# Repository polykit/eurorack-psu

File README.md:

# Eurorack Power Supply

This repository contains KiCad schematics and PCB layout for an Eurorack power supply. It delivers +12V, -12V and +5V. A 12V AC/AC 1A to 2A wall wart power supply is needed. Gerber files can be found [here](plots/)

## BOM

|Reference               |Quantity|Value                                             |
|------------------------|--------|--------------------------------------------------|
|C1 C2 C3 C4 C5 C6       |6       |3300uF                                            |
|C9 C10 C12              |3       |100uF                                             |
|C7 C8 C11               |3       |1uF                                               |
|D1 D2 D3 D4 D5 D6 D7 D8 |8       |1N4004                                            |
|D9                      |1       |LED 5mm                                           |
|J1                      |1       |Barrel Jack Socket 5.5mm/2.1mm                    |
|J2                      |1       |IDC 16-pin                                        |
|J3                      |1       |2-pin 5.4mm**                                     |
|J4                      |1       |IDC 10-pin                                        |
|R1 R2                   |2       |3k3*                                              |
|R3                      |1       |330                                               |
|U1                      |1       |L7812                                             |
|U2                      |1       |L7912                                             |
|U3                      |1       |L7805                                             |
|Heatsink                |3       |for TO-220 (max. size 30mm x 13mm) eg. SK 145/37,5|

\* load resistors can be omitted

\** alternative connector to barrel jack

## References

http://musicfromouterspace.com/analogsynth_new/WALLWARTSUPPLY/WALLWARTSUPPLY.php

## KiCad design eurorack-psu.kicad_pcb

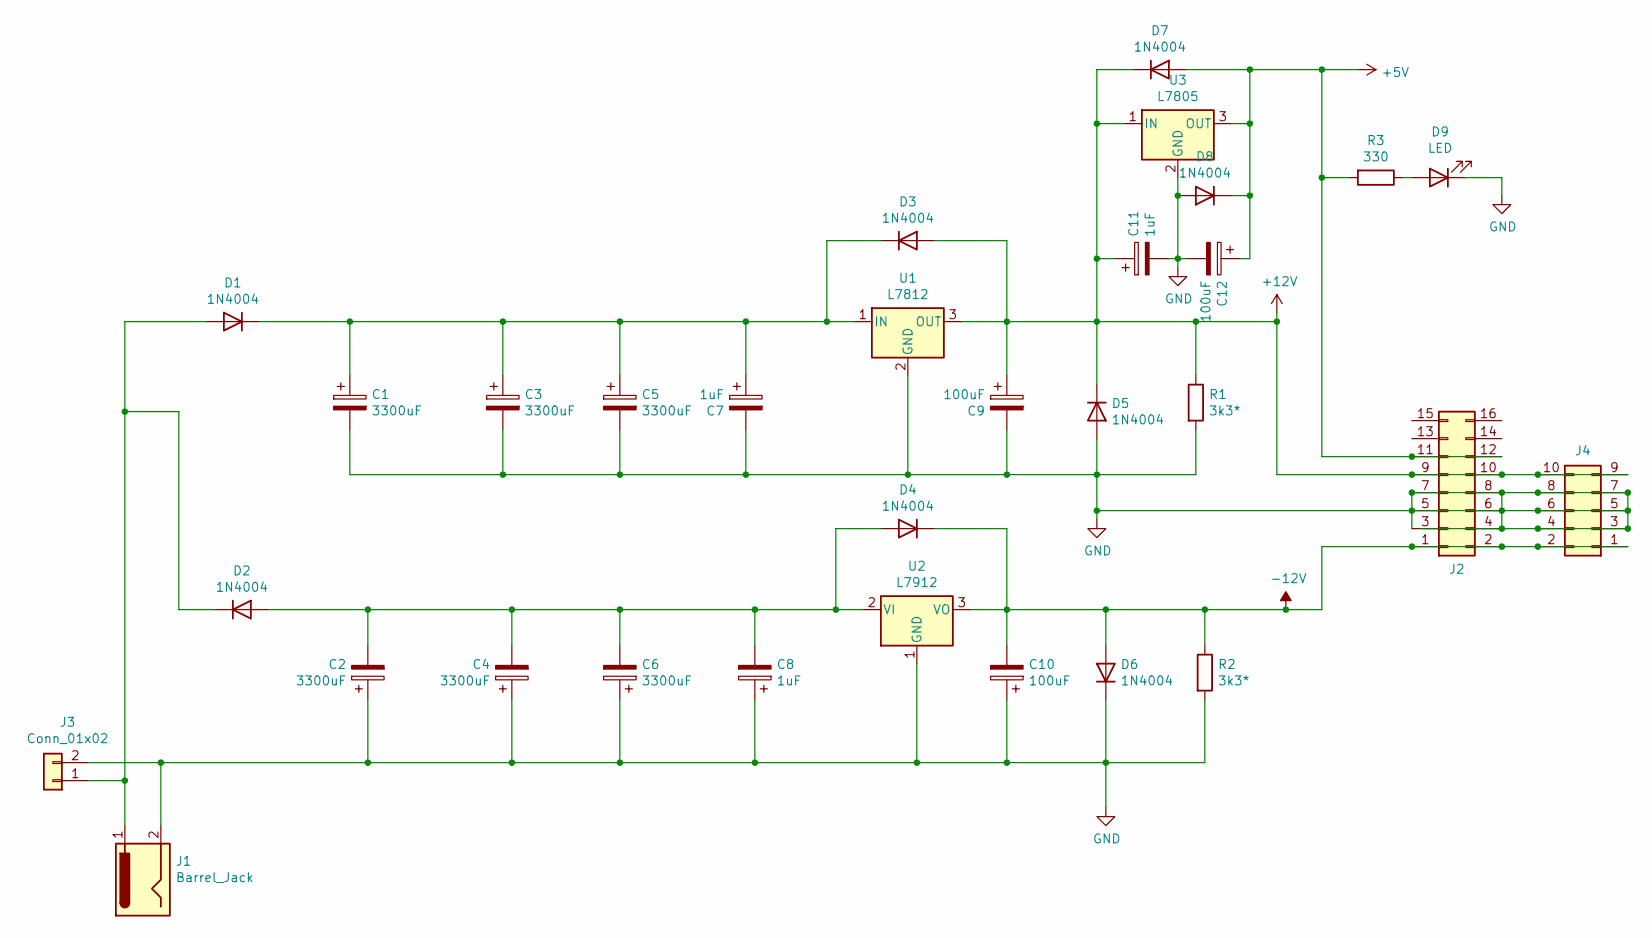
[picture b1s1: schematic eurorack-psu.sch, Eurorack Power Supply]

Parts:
C1, C2, C3, C4, C5, C6: 3300uF; CP_Radial_D18.0mm_P7.50mm
C7, C8, C11: 1uF; CP_Radial_D5.0mm_P2.50mm
C9, C10, C12: 100uF; CP_Radial_D6.3mm_P2.50mm
D1, D2, D3, D4, D5, D6, D7, D8: 1N4004; D_DO-41_SOD81_P10.16mm_Horizontal
D9: LED; LED_D5.0mm
J1: Barrel_Jack; BarrelJack_Horizontal
J2: Connector_Generic:Conn_02x08_Odd_Even; IDC-Header_2x08_P2.54mm_Vertical
J3: Conn_01x02; SolderWire-1sqmm_1x02_P5.4mm_D1.4mm_OD2.7mm
J4: Conn_02x05_Odd_Even; IDC-Header_2x05_P2.54mm_Vertical
R1, R2: 3k3*; R_Axial_DIN0207_L6.3mm_D2.5mm_P10.16mm_Horizontal
R3: 330; R_Axial_DIN0207_L6.3mm_D2.5mm_P10.16mm_Horizontal
U1: L7812; TO-220-3_Vertical
U2: L7912; TO-220-3_Vertical
U3: L7805; TO-220-3_Vertical

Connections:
+5V: C12.1, D7.2 (A), D8.1 (K), J2.11, J2.12, R3.2, U3.3 (OUT)
+12V: C9.1, C11.1, D3.2 (A), D5.1 (K), D7.1 (K), J2.9, J2.10, J4.9, J4.10, R1.1, U1.3 (OUT), U3.1 (IN)
-12V: C10.2, D4.1 (K), D6.2 (A), J2.1, J2.2, J4.1, J4.2, R2.1, U2.3 (VO)
GND: C1.2, C2.1, C3.2, C4.1, C5.2, C6.1, C7.2, C8.1, C9.2, C10.1, C11.2, C12.2, D5.2 (A), D6.1 (K), D8.2 (A), D9.1 (K), J1.2, J2.3, J2.4, J2.5, J2.6, J2.7, J2.8, J3.2, J4.3, J4.4, J4.5, J4.6, J4.7, J4.8, R1.2, R2.2, U1.2 (GND), U2.1 (GND), U3.2 (GND)
unnamed: C1.1, C3.1, C5.1, C7.1, D1.1 (K), D3.1 (K), U1.1 (IN)
unnamed: C2.2, C4.2, C6.2, C8.2, D2.2 (A), D4.2 (A), U2.2 (VI)
unnamed: D1.2 (A), D2.1 (K), J1.1, J3.1
unnamed: D9.2 (A), R3.1

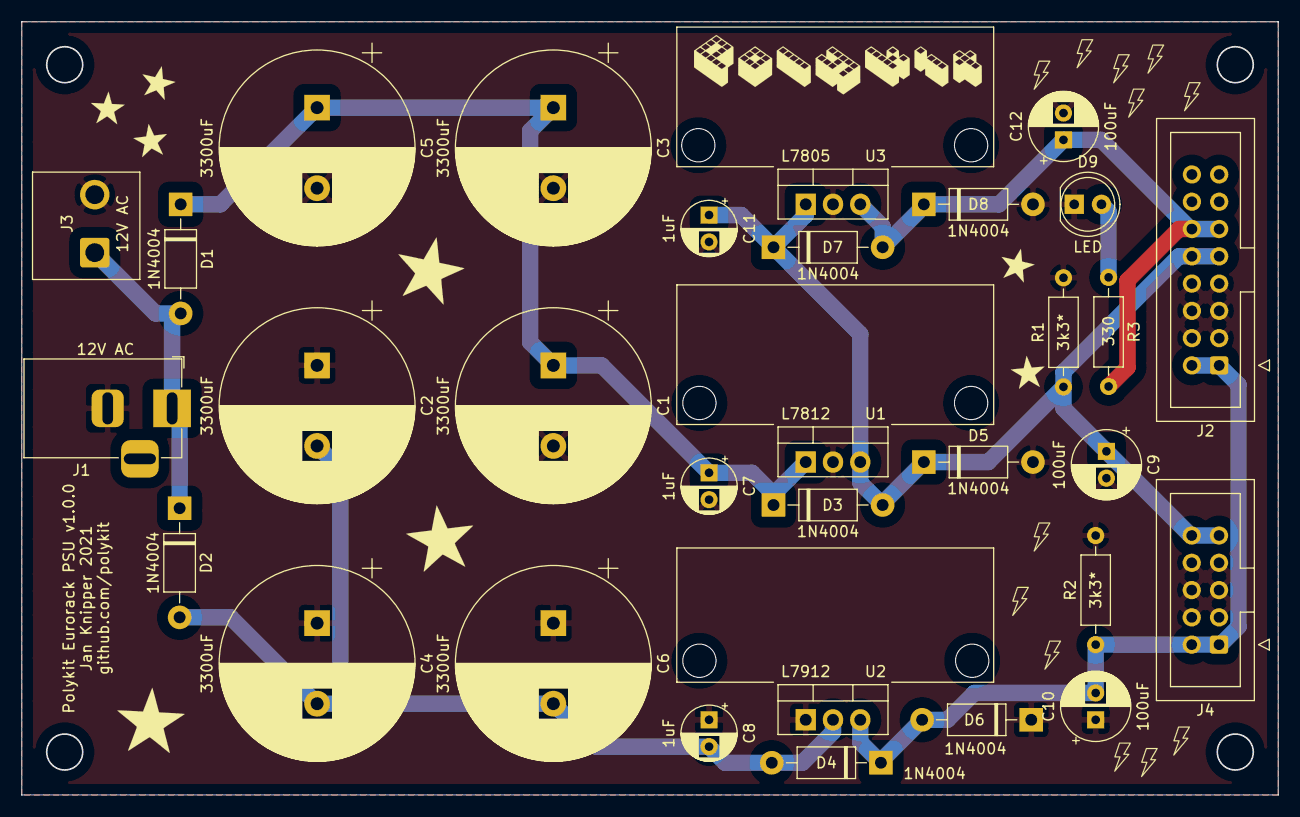
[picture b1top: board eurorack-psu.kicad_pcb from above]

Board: 2 copper layers, 117.0 x 72.0 mm, 31 parts (0 on the bottom side), 8 nets.
